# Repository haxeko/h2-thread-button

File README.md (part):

# ESP32-H2 Matter over Thread: nút nhấn chạy pin (CR2450 hoặc CR123A)

Thiết kế đầy đủ (phần cứng, firmware, tính pin, kiểm thử) cho một **nút nhấn Matter over Thread chạy một viên pin lithium 3 V**: module **ESP32-H2-WROOM-02C**, một nút nhấn vật lý, gửi **nhấn một lần / nhấn đúp / giữ lâu** dưới dạng sự kiện chuẩn của cluster **Switch** (device type Generic Switch 0x000F), dùng được trong Apple Home, Home Assistant và các controller Matter khác. Thiết bị là **Thread Sleepy End Device (SED)** kiêm **Matter Intermittently Connected Device (ICD)**: ngủ Light-sleep giữa các lần nhấn mà vẫn giữ kết nối Thread, thức dậy bằng ngắt của nút.

Ba bản phần cứng, cùng mạch và cùng mã firmware, khác nhau ở pin, đế pin, tụ bulk và bố trí; bản mini còn đổi hai chân GPIO ([`hardware/`](hardware/README.md)):

| Bo | Pin | Bo (cả anten) | Tuổi pin dự tính, SIT / LIT (20 lần nhấn/ngày) | Firmware |
|---|---|---|---|---|
| [`hardware/module-cr2450`](hardware/module-cr2450/README.md) | **CR2450** 620 mAh, đế Keystone 3008 | 37,4 × 36,5 mm | ~11 / ~15 tháng | mặc định |
| [`hardware/module-cr123a`](hardware/module-cr123a/README.md) | **CR123A** 1500 mAh, đế Bulgin BX0123 | 42,4 × 33,5 mm | ~30 / ~41 tháng | `sdkconfig.defaults.cr123a` |
| [`hardware/module-cr123a-mini`](hardware/module-cr123a-mini/README.md) | **CR123A** 1500 mAh trong vỏ, dọc cạnh dưới bo (tiếp điểm của vỏ nối dây vào pad BAT+/BAT− ở mép dưới; nút ở mép trên) | **34,5 × 20,8 mm**: dài đúng một viên CR123A | ~30 / ~41 tháng | `sdkconfig.defaults.cr123a_mini` |

Firmware ([`firmware/`](firmware)): ESP-IDF v6.0.2 + esp-matter release/v1.6.1. Các biến thể: mặc định (bo CR2450, ICD SIT), `lit`, `cr123a`, `cr123a_mini`, `unique_setup`, `factory`, `pmdiag`, `debug`. Host test chạy được không cần ESP-IDF: máy trạng thái nút (17 kịch bản), gửi lại cử chỉ, cách báo % pin. **Chưa đo trên bo thật**: mọi số đo đánh dấu [AS] phải được thay bằng số đo theo [checklist](docs/test-checklist.md).

Bản cũ dùng pin CR2032 (bo 29,8 × 23,9 mm, Keystone 3034) và bo chip ESP32-H2 không dùng module (`hardware-chip/`) đã bỏ khỏi repo: tuổi pin CR2032 chỉ 4–5,5 tháng (mục 1.6). Xem lịch sử git, commit `dad9ded` là bản cuối có cả hai. Firmware cảm biến cửa [`matter-door-sensor`](https://github.com/haxeko/esp32-iot-project/tree/claude/matter-button-cr2032/ESP32-H2/matter-thread/matter-door-sensor) (repo esp32-iot-project) viết cho bo CR2032 cũ; mạch giống hệt nên chạy được trên các bo này (công tắc lưỡi gà hàn song song SW1; bo mini cần đổi chân LED và đo pin như mục 2.3).

> **Kết luận nhanh**
>
> - Pin lithium 3 V (Li-MnO2: CR2450, CR123A) **không cấp trực tiếp** được cho ESP32-H2 (VDD tối thiểu 3,0 V; pin chỉ ~2,85–3,0 V khi có tải và giảm dần về 2,0 V). Bắt buộc có **buck-boost TPS63900** (Iq 75 nA). CR2450 có điện trở trong 8–30 Ω nên cần thêm **tụ bulk ≥ 220 µF hiệu dụng** trên đường pin; CR123A dưới 1 Ω, không cần.
> - Dòng ngủ: ESP32-H2 Light-sleep 25–27 µA ở 3,3 V → **~35 µA tại pin**: đạt mục tiêu < 50 µA. Riêng mức sàn này đã giới hạn tuổi pin ở tối đa **~19 tháng (CR2450)** và **~51 tháng (CR123A)** dù không nhấn lần nào.
> - Tuổi pin dự tính (TX 0 dBm, 1 controller, 5–100 lần nhấn/ngày): **CR2450: 10,4–11,3 tháng ở SIT** (mặc định, chạy với mọi controller kể cả Apple Home), **12,2–15,7 tháng ở LIT** (Home Assistant có Battery Saver; Apple Home hiện chưa hỗ trợ). **CR123A: 28–31 tháng ở SIT, 33–43 tháng ở LIT.** Mục tiêu 6–12 tháng đạt với cả hai (CR2450 ở SIT sát 12 tháng).
> - Chọn bo: **CR2450** khi cần gọn (pin dày 5 mm, bo 37,4 × 30,5 mm); **CR123A** khi cần ~2,5 năm và chịu lạnh tốt hơn (pin Ø17 × 34,5 mm, bo 42,4 × 27,5 mm).
> - Phản hồi: sự kiện đầu tiên (`InitialPress`) rời anten **~25–40 ms** sau khi nhấn; sự kiện "nhấn một lần" mà Apple Home / Home Assistant dùng (`MultiPressComplete`) đi ra **350 ms sau khi nhả** (cửa sổ phân biệt nhấn đúp, chỉnh được; tắt nhấn đúp thì có ngay).

## Mục lục

1. [Đánh giá khả thi](#1-đánh-giá-khả-thi)
2. [Kiến trúc phần cứng](#2-kiến-trúc-phần-cứng)
3. [Sơ đồ nguyên lý và bảng kết nối](#3-sơ-đồ-nguyên-lý-và-bảng-kết-nối)
4. [BOM](#4-bom)
5. [Cấu hình Thread SED + Matter ICD](#5-cấu-hình-thread-sed--matter-icd)
6. [Thuật toán nút nhấn](#6-thuật-toán-nút-nhấn)
7. [Firmware](#7-firmware)
8. [Build, flash, commissioning (Windows PowerShell)](#8-build-flash-commissioning-windows-powershell)
9. [Bảng tính thời lượng pin](#9-bảng-tính-thời-lượng-pin)
10. [Rủi ro và cách khắc phục](#10-rủi-ro-và-cách-khắc-phục)

Cấu trúc repo:

```
h2-thread-button/
├── README.md                 tài liệu chính (file này)
├── firmware/                 dự án ESP-IDF / esp-matter, chung cho mọi bo (mục 7)
├── hardware/                 các bo KiCad, mỗi bo một thư mục + bộ script sinh dùng chung (hardware/README.md)
│   ├── scripts/
│   ├── module-cr2450/
│   ├── module-cr123a/
│   └── module-cr123a-mini/
├── docs/                     test-checklist.md, sơ đồ nguyên lý (ảnh)
└── tools/                    mô hình pin, mô phỏng tụ bulk, vẽ sơ đồ, công cụ factory data (matter-mfg)
```

Kiểm thử: [`docs/test-checklist.md`](docs/test-checklist.md). PCB KiCad và file sản xuất: [`hardware/`](hardware/README.md).

Ký hiệu nguồn số liệu dùng trong toàn tài liệu: **[DS]** datasheet; **[ME]** số đo công bố của Espressif (esp-matter `examples/icd_app`, ESP32-H2 DevKitC); **[AS]** giả định / ước lượng, phải đo lại trên bo thật.

---

## 1. Đánh giá khả thi

### 1.1 Số liệu đầu vào

| Thông số | Giá trị | Nguồn |
|---|---|---|
| CR2450: điện áp danh định, dung lượng | 3,0 V; 620 mAh tới 2,0 V (Energizer, Panasonic, Murata; Renata CR2450N 540 mAh) | [DS] |
| CR2450: điện áp có tải | ~2,9 V phần lớn đời pin ở tải nhẹ; tụt nhanh sau ~85 % dung lượng | [DS] đồ thị xả |
| CR2450: điện trở trong | ~8–10 Ω khi mới, ~12–15 Ω giữa đời, 20–30 Ω gần cuối; ×2–2,5 ở −10 °C | [AS] đường IR của CR2032 (Energizer) chia theo diện tích điện cực (`tools/capsim.py`) |
| CR123A (IEC CR17345): điện áp, dung lượng | 3,0 V; 1400–1550 mAh tới 2,0 V (Panasonic CR123A, Energizer EL123AP, Duracell) | [DS] |
| CR123A: điện trở trong | ~0,1–0,3 Ω khi mới, dưới 1 Ω gần suốt đời pin; chịu xung 1–2 A | [DS] đồ thị xung / [AS] |
| Tự xả, nhiệt độ | ~1 %/năm; −30…60 °C (CR2450), −40…60 °C (CR123A) | [DS] |
| ESP32-H2: điện áp cấp (VDD3P3, VBAT, VDDPST) | **3,0–3,6 V** (typ 3,3 V) | [DS] ESP32-H2 v1.3, Bảng 5-2 |
| ESP32-H2: TX 802.15.4 | 36 mA @ 0 dBm; 60 mA @ 9 dBm; **140 mA @ 20 dBm** | [DS] Bảng 5-7 |
| ESP32-H2: RX 802.15.4 / BLE | 25 mA / 24 mA | [DS] Bảng 5-6, 5-7 |
| ESP32-H2: CPU 96 MHz, clock ngoại vi tắt | 10 mA chạy, 6 mA idle | [DS] Bảng 5-8 |
| ESP32-H2: Light-sleep (CPU, radio, ngoại vi số tắt nguồn) | **25 µA** typ (85 µA nếu giữ ngoại vi) | [DS] Bảng 5-9 |
| ESP32-H2: Light-sleep đo thực tế | 26,7–27,0 µA | [ME] |
| ESP32-H2: Deep-sleep | 7 µA (mất RAM, mất kết nối Thread) | [DS] |
| ESP32-H2: brownout | mức 7 ≈ 2,94 V (firmware chọn mức này) | ESP-IDF Kconfig |
| ESP32-H2: ADC, ATTEN 12 dB | 0–3300 mV, sai số ±23 mV sau hiệu chuẩn; dòng rò chân ≤ 50 nA | [DS] |
| TPS63900: dải vào, UVLO | 1,8–5,5 V; UVLO lên 1,75 V typ, trễ 0,1 V → tắt ở ~1,65 V | [DS] TI SLVSET3D |
| TPS63900: dòng tĩnh | 75 nA typ, 1 µA max | [DS] |
| TPS63900: hiệu suất, 3,3 V ra | ~89–91 % (VIN 2,5–3,3 V, tải 10 µA–10 mA); ~87 % ở VIN 1,8 V | [DS] Hình 8-7 |

### 1.2 Pin lithium 3 V có cấp trực tiếp cho ESP32-H2 được không? Không

1. **Điện áp.** ESP32-H2 cần ≥ 3,0 V. Pin Li-MnO2 (CR2450, CR123A) chỉ 3,0–3,3 V khi hở mạch lúc còn mới, ~2,85–3,0 V khi có tải và giảm dần về 2,0 V. Nối trực tiếp thì chip chạy **ngoài thông số ngay từ đầu**, và brownout (mức thấp nhất 2,57 V) cắt khi pin còn phần lớn dung lượng. Điều này đúng cả với CR123A dù pin chịu dòng tốt.
2. **Dòng (CR2450).** Xung TX/RX 25–36 mA (0 dBm) qua điện trở trong 8–30 Ω gây sụt 0,2–1 V; ở +20 dBm (140 mA, mặc định của driver ESP-IDF) sụt 1–4 V → reset ở mỗi khung phát. CR123A (< 1 Ω) chỉ sụt vài chục mV.
3. **Chân VBAT của module không phải đầu vào pin.** Trong WROOM-02C, chân 14 (VBAT) nối sẵn vào 3V3 qua điện trở 0 Ω (datasheet module, mục 8: *"When VBAT is powered by external battery, R2 can be NC"*). Đưa pin vào chân này là chập pin với đường 3V3.

→ Cần bộ **buck-boost** giữ 3,3 V khi pin đi từ 3,2 V xuống ~1,8 V. LDO không dùng được (pin < 3,3 V). Boost thuần không hạ áp được khi pin mới (3,2 V gần bằng đầu ra). Chọn **TI TPS63900**: Iq 75 nA (≈ 0,2 % của mức sàn 35 µA), hiệu suất ~90 % ở dòng µA–mA, đầu vào tới 1,8 V.

### 1.3 Dòng rút từ pin khi phát/thu

Bộ buck-boost là **tải công suất không đổi**: I_pin = I_3V3 × 3,3 V / (η × V_pin). Pin càng yếu, dòng rút càng lớn.

| Trạng thái (dòng ở 3,3 V [DS]) | V_pin 2,9 V | V_pin 2,4 V | V_pin 2,0 V |
|---|---|---|---|
| TX 0 dBm (36 mA) | 46 mA | 55 mA | 68 mA |
| RX (25 mA) | 32 mA | 38 mA | 47 mA |
| CPU 96 MHz (10 mA) | 13 mA | 15 mA | 19 mA |
| TX +9 dBm (60 mA) | 76 mA | 92 mA | 114 mA |
| TX +20 dBm (140 mA) | 177 mA | 214 mA | 266 mA |

(η = 0,90 ở 2,9 V và 2,4 V; 0,87 ở 2,0 V.) **Firmware giữ TX ở 0 dBm** (`THREAD_TX_POWER_DBM`) và áp dụng ngay khi driver 802.15.4 khởi tạo, trước khung đầu tiên (mục [5.6](#56-công-suất-phát)). BLE (chỉ dùng lúc ghép nối) cũng đặt 0 dBm.

### 1.4 Sụt áp, tụ bulk và brownout khi phát

Mô hình: pin = nguồn V_oc nối tiếp R_trong. TPS63900 tắt khi V_pin < ~1,65 V (UVLO), lúc đó 3V3 sập và ESP32-H2 brownout.

**CR2450** (bo `module-cr2450`):

- **Không có tụ bulk**, pin đã dùng ~80 % (V_oc ≈ 2,8 V, R ≈ 20 Ω [AS]): xung TX 0 dBm 55 mA → sụt 1,1 V → V_pin ≈ 1,7 V, sát UVLO; lạnh hoặc pin kém hơn thì **reset ở mỗi lần phát**.
- **Có tụ bulk C trên đường pin** (trước buck-boost): tụ cấp phần lớn xung ngắn, pin nạp lại tụ qua R. Sụt áp sau thời gian t: ΔV = I·R·(1 − e^(−t/RC)). Khung 802.15.4 dài nhất 127 byte = **4,3 ms** ở 250 kbit/s. Với C = 260 µF hiệu dụng, R = 20 Ω (τ = 5,2 ms): ΔV = 1,1 V × (1 − e^(−0,83)) = **0,62 V** → V_pin ≈ 2,2 V > UVLO. Thiết kế dùng **2 × 220 µF 1210 X5R** (≈ 260 µF hiệu dụng ở 3 V sau DC-bias [AS], kiểm tra bằng Murata SimSurfing hoặc đo).
- Đặt tụ **phía pin** (được phép sụt từ 2,9 V xuống ~1,8 V) dùng năng lượng tụ hiệu quả hơn nhiều so với phía 3,3 V (chỉ được sụt 0,3 V trước brownout 2,94 V).
- **Thu liên tục** khi re-attach Thread (Parent Request tới router rồi tới REED: 0,75 s + 1,25 s ≈ 2 s RX) thì không tụ nào bù được: pin phải tự cấp ~95 mW (25 mA × 3,3 V / η). Giữ V_pin ≥ 1,75 V đòi hỏi R_trong ≤ ~20 Ω (V_oc 2,8 V). Mô hình pin vì vậy chỉ tính **80 % dung lượng danh định** (496 mAh) [AS]. Qua mức đó nút vẫn chạy (xung ngắn vẫn có tụ đỡ), nhưng một lần re-attach (mất Border Router, khởi động lại) có thể gây brownout.

**CR123A** (bo `module-cr123a`): R_trong dưới 1 Ω gần suốt đời pin, nên mọi xung (TX, RX 2 s, khởi động) chỉ sụt 0,05–0,4 V. Mô phỏng `tools/capsim.py` [AS] cho V_pin thấp nhất ≥ 2,55 V khi khởi động hoặc re-attach ở mọi trạng thái pin tới −10 °C, **có hay không có tụ bulk**. Bo chỉ có 1 × 100 µF (lọc gần đầu vào, đường VBAT dài) cùng 10 µF ở VIN của TPS63900. Mô hình tính **90 %** dung lượng (1350 mAh).

**Firmware bảo vệ thêm (mọi bo):** brownout 2,94 V trên đường 3,3 V; bộ đếm brownout và đo áp lúc khởi động → Deep-sleep 1 giờ khi pin quá yếu (không reset lặp vô hạn); từ chối tải OTA khi pin không ở mức OK; đo điện trở trong mỗi ngày để báo pin yếu **trước** khi sập (mục [2.5](#25-đo-pin-gần-như-không-tốn-dòng)).

### 1.5 Dòng ngủ là giới hạn chính

Dòng trung bình, SIT 15 s, 20 lần nhấn/ngày, 1 controller (`tools/battery_model.py --breakdown`):

| Thành phần | Tại 3,3 V | Tỷ lệ |
|---|---|---|
| Light-sleep ESP32-H2 | 27,0 µA | 58,6 % |
| Data poll mỗi 15 s (0,25 mC/lần) | 16,7 µA | 36,2 % |
| Report keep-alive mỗi giờ | 0,9 µA | 1,9 % |
| Bảo trì Thread/Matter (SRP, MLE, đo pin, hỏi OTA) | 0,7 µA | 1,5 % |
| 20 lần nhấn/ngày | 0,9 µA | 1,9 % |
| **Tổng tại 3,3 V** | **46,1 µA** | |
| **Tại pin** (× 3,3 / (0,89 × V_pin) + Iq + rò) | **60 µA** (CR2450) / **59 µA** (CR123A) | → **11,2 tháng** / **30,4 tháng** |

Chỉ riêng Light-sleep (không poll, không nhấn) đã là ~35 µA tại pin → trần **~18,8 tháng** với CR2450 (496 mAh dùng được), **~51 tháng** với CR123A (1350 mAh). Với CR2450, muốn ≥ 12 tháng ở SIT thì dòng trung bình tại pin phải ≤ ~56 µA: dùng LIT (chỉ Home Assistant), hoặc bo CR123A.

**Vì sao không dùng Deep-sleep (7 µA)?** Deep-sleep tắt RAM, mất trạng thái Thread và phiên Matter. Mỗi lần nhấn sẽ phải khởi động lại, attach Thread (≥ 2 s thu), mở lại phiên CASE và subscription (vài giây): **không đạt < 300 ms**, controller thấy thiết bị offline giữa các lần nhấn, và mỗi lần nhấn tốn 60–200 mC (bằng 2–8 giờ Light-sleep).

### 1.6 Kết luận và phương án

| Mục tiêu | Thiết kế này | Đạt? |
|---|---|---|
| Dòng ngủ < 50 µA | 27 µA tại 3,3 V; ~35 µA tại pin | ✅ |
| Phản hồi < 300 ms | `InitialPress` rời anten ~25–40 ms sau khi nhấn; "nhấn một lần" = lúc nhả + 350 ms (chỉnh được, mục [6.6](#66-độ-trễ)) | ✅ có điều kiện |
| Pin 6–12 tháng | CR2450: SIT 10,4–11,3 tháng, LIT 12,2–15,7 tháng; CR123A: SIT 28–31 tháng, LIT 33–43 tháng | ✅ (CR2450 ở SIT sát 12 tháng) |

Các nguồn pin đã xét (20 lần nhấn/ngày, 1 controller, cùng mạch và firmware, `tools/battery_model.py`):

| Nguồn | SIT 15 s (Apple + HA) | LIT 120 s (HA Battery Saver) | Ghi chú |
|---|---|---|---|
| **CR2450** (bo `module-cr2450`) | **11,2 tháng** | **15,0 tháng** | 620 mAh × 0,80; Ø24,5 × 5,0 mm; bo gọn nhất |
| **CR123A** (bo `module-cr123a`, `module-cr123a-mini`) | **30,4 tháng** | **40,7 tháng** | 1500 mAh × 0,90; Ø17 × 34,5 mm; chịu xung và lạnh tốt |
| CR2032 (bo cũ, đã bỏ) | 4,0 tháng | 5,4 tháng | 220 mAh × 0,80: lý do bỏ |
| 2 × AAA alkaline (chưa có bo) | ~19 tháng | ~26 tháng | TPS63900 chạy tới 1,8 V (0,9 V/cell); pin alkaline có thể chảy |
| CR2450 + SoC dòng ngủ ~2 µA | 23,9 tháng | 53,4 tháng | chỉ đổi mức sàn, vẫn giữ chi phí poll của ESP32-H2 (phải thiết kế lại phần cứng và firmware) |

---

## 2. Kiến trúc phần cứng

### 2.1 Sơ đồ khối

```
            Q1 P-FET                 VBAT (1,8 .. 3,2 V)                   3V3
 Pin ─────► chống ngược ──JP1──┬────────────────┬──► TPS63900 ──JP2──┬──► ESP32-H2-WROOM-02C
 (BT1)      cực              C1(+C2)          R9 1 MΩ   buck-boost       │      GPIO10 ◄── SW1 (LP IO, EXT1 wake)
 CR2450 /                    tụ bulk           │        3,3 V, Iq 75 nA  │      GPIO22 ──► LED D1
 CR123A                      (theo bo)         └──────── VBAT_SENSE ─────┼────► GPIO1 (ADC1_CH0)
                                                                         │      UART0, EN, BOOT, USB ──► pad nạp/debug
                                                                       C4..C6
```

| Khối | Nhiệm vụ |
|---|---|
| Q1 (P-MOSFET) | chống lắp ngược pin, sụt ~5 mV (R_DS(on) ~0,1 Ω ở 50 mA) thay vì 0,3 V của diode Schottky |
| JP1, JP2 (cầu hàn) | điểm cắt để đo dòng pin (JP1) và dòng đường 3,3 V (JP2); mặc định nối |
| C1, C2 | tụ bulk, cấp xung TX/RX ngắn, giảm sụt áp trên điện trở trong của pin (mục 1.4): bo CR2450 2 × 220 µF; bo CR123A chỉ C1 100 µF; bo CR123A mini chỉ C1 22 µF |
| TPS63900 | buck-boost 3,3 V, Iq 75 nA, chạy từ 1,8 V |
| R9 + C9 | đo áp pin không tốn dòng (mục 2.5) |
| SW1 + R6/R7/C8 | nút nhấn, lọc RC, kéo lên 1 MΩ (mục 2.4) |
| D1 + R8 | LED trạng thái (ghép nối, Identify, xác nhận reset, pin yếu); chỉ nháy ngắn |

### 2.2 Đường nguồn

- **Q1 AO3401A** nối kiểu "ideal diode": D về pin, S về VBAT, G xuống GND. Lắp đúng: diode thân dẫn trước, V_GS = −V_pin → FET mở. Lắp ngược: V_GS = 0, diode thân phân cực ngược → không có dòng. Cần thiết vì cả hai đế đều lắp ngược pin được: với đế Keystone 3008 (CR2450), lá kẹp (+) chạm mặt trên của pin, lắp úp pin thì mặt (−) chạm lá kẹp (+), mặt (+) chạm pad GND; đế Bulgin BX0123 (CR123A) cho cắm ngược đầu pin.
- **TPS63900** (theo mạch điển hình 3,3 V của datasheet, Hình 8-1 / Bảng 8-5):
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
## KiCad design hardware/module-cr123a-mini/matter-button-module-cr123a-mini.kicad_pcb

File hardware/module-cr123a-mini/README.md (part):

# Bo module-cr123a-mini: nút nhấn Matter dài đúng một viên CR123A

Bản gọn của [`module-cr123a`](../module-cr123a/README.md): bo **dài 34,5 mm, bằng chiều dài pin CR123A**, cao 14,8 mm. Anten module chìa ra 6 mm ở mép trên, **cả cụm 34,5 × 20,8 mm**. **Nút nhấn SW1 và LED ở mép trên (phía anten)**, góc trái, xa anten nhất. Pin **không nằm trên bo**: pin nằm trong ngăn pin của vỏ, **dọc cạnh dưới bo** (cạnh không có anten); hai tiếp điểm của vỏ nối dây vào hai pad **BAT+ / BAT−** ở hai đầu mép dưới, mặt dưới bo.

Mọi file được sinh bằng các script dùng chung trong [`../scripts`](../README.md) từ [`design.py`](design.py), rồi kiểm tra bằng KiCad 9.0.9:

- **ERC: 0 lỗi, 0 cảnh báo.**
- **DRC: 0 vi phạm, 0 pad chưa nối, 0 lỗi footprint, 0 lệch giữa PCB và schematic.**
- **Mọi đường mạch đều vẽ tay** trong `design.py`, không qua FreeRouting: sinh lại lúc nào cũng ra đúng bo này.

Chưa đặt mạch, chưa đo trên bo thật. Firmware: **`sdkconfig.defaults.cr123a_mini`**, không dùng bản `cr123a` vì LED và chân đo pin khác (mục 2).

| Mặt trên | Mặt dưới |
|---|---|
|  |  |

Đồng và silkscreen (mặt dưới nhìn từ dưới lên, đã lật):

## 1. Khác bo module-cr123a

| | `module-cr123a` | `module-cr123a-mini` |
|---|---|---|
| Bo / cả cụm có anten | 42,4 × 27,5 / 42,4 × 33,5 mm | **34,5 × 14,8 / 34,5 × 20,8 mm** |
| Pin | trong đế Bulgin BX0123 ở mặt dưới bo | trong vỏ, dọc cạnh dưới bo; tiếp điểm của vỏ nối dây vào pad BAT+ / BAT− ở mép dưới |
| Nút SW1, LED | SW1 ở dải dưới, giữa; LED dưới module, cạnh chân 15 | **mép trên (phía anten), góc trái**; LED ngay bên phải nút |
| Lắp ráp | linh kiện mặt trên, đế pin mặt dưới | **chỉ mặt trên**; mặt dưới chỉ có đồng: 2 pad pin, 8 pad test |
| LED / đo pin | GPIO22 (chân 15) / GPIO1 (chân 27, ADC1_CH0) | **GPIO11 (chân 6) / GPIO4 (chân 3, ADC1_CH3)** |
| Đo dòng | cầu hàn JP1 (pin), JP2 (3,3 V) | **mắc ampe kế nối tiếp dây BAT+**; không có JP1, JP2 |
| Tụ VBAT | C1 100 µF 1206 | C1 22 µF 0603 (cùng mã với C4) |
| C7 (tụ EN, không lắp) | có footprint | bỏ (module đã có RC trên EN) |
| Pad test | 10 (thêm VBAT, VBAT_SENSE) | 8: 3V3, GND, TX, RX, EN, BOOT, USB D−, D+ (VBAT đo ở C1, VBAT_SENSE ở C9) |
| Firmware | `sdkconfig.defaults.cr123a` | `sdkconfig.defaults.cr123a_mini` |
| Tuổi pin dự tính | ~30 tháng (SIT), ~41 tháng (LIT) | như bản kia: cùng pin, cùng mạch |

## 2. Vì sao đổi chân LED và đo pin

Mọi linh kiện phải nằm ở mặt trên, trong vùng 15 × 14,2 mm bên trái module. Chân 15 (GPIO22) nằm ở cạnh dưới module, sát mép dưới bo, không còn chỗ thoát dây. Chân 27 (GPIO1) nằm ở cạnh phải module, xa phần mạch. Bo này chỉ dùng các chân ở cạnh trái module:

| Chân module | GPIO | Dùng cho |
|---|---|---|
| 1 | 3V3 | nguồn, C6 |
| 2 | EN | R4, pad test EN |
| 3 | **GPIO4 (ADC1_CH3)** | **đo pin**: R9 1 MΩ từ VBAT, C9 100 nF |
| 5 | GPIO10 | nút (LP IO, đánh thức EXT1), như các bo khác |
| 6 | **GPIO11** | **LED**: R8 1 kΩ → D1 |
| 7 | GPIO8 | R5 kéo lên (strapping) |
| 8 | GPIO9 | BOOT, pad test |

GPIO4 là chân JTAG MTCK. Lúc chạy, driver ADC đặt chân ở chế độ analog (không có điện trở kéo), và trong Light-sleep firmware cô lập mọi GPIO. Chỉ lúc khởi động hay Deep-sleep, nếu chân có điện trở kéo mặc định thì tốn tối đa vài µA qua R9: cần đo (checklist, mục P). GPIO11 là LP IO thường, không phải chân strapping hay JTAG.

## 3. Thông số bo

| Mục | Giá trị |
|---|---|
| Kích thước | **34,5 × 14,8 mm**, góc bo R0,5; anten module nhô 6 mm khỏi mép trên → **34,5 × 20,8 mm**; không có lỗ |
| Lớp | 2 lớp FR-4 1,6 mm, đồng 1 oz |
| Đường mạch | 0,2 mm tín hiệu, 0,25–0,5 mm nguồn; khe hở ≥ 0,2 mm; via 0,6 / 0,3 mm phủ mask |
| Cách mép bo | đồng ≥ 0,3 mm |
| Bề mặt | ENIG khuyến nghị (WSON bước 0,5 mm, pad hàn dây) |
| Linh kiện | **mặt trên tất cả** (lắp ráp một mặt) |
| Mặt dưới | pad BAT+ 3,6 × 1,6 mm và pad BAT− 2,8 × 1,6 mm dọc mép dưới, ở hai đầu (BAT− nằm trong vùng phủ GND), 8 pad test Ø1,5 mm dưới module, phủ đồng GND |

## 4. Bố trí

| Vùng (nhìn từ mặt trên) | Linh kiện |
|---|---|
| Mép trên, góc trái (phía anten) | SW1, LED D1 ngay bên phải nút; thân nút cách mép trái module (và anten) hơn 10 mm. Đường nút chạy dọc mép trên, qua phía trên D1, xuống ở x = 10,2 mm tới R7; đường LED xuống ở x = 9,6 mm tới R8 |
| Giữa, bên trái | TPS63900: L1 sát mép trái, C4 (3V3) phía trên, C3 (VIN) phía dưới, R1–R3 bên phải; cùng mạch như các bo khác, xoay 90° theo chiều kim đồng hồ, C3 và C4 sát U2 hơn. C5 (3V3) giữa nút và L1 |
| Mép dưới, bên trái | Q1 + C1: đầu vào pin, cực D của Q1 ngay trên pad BAT+ (mặt dưới); đường VBAT dọc y = 10,6 mm nối Q1, C3, C1, chân SEL/EN của U2 |
| Cạnh trái module | mỗi chân một hàng: C6 (chân 1), R4 (chân 2), R9 + C9 (chân 3), R7 + C8 (chân 5), R8 (chân 6), R5 (chân 7); R6 (kéo lên nút) ở trên cùng, giữa đường nút và trục 3V3 theo mép trên tới chân 1 |
| Mặt dưới | BAT+ và BAT− dọc mép dưới, ở hai đầu; pad test dưới module; 3V3 từ bộ nguồn sang góc module (rồi tới TP1 và xuống R5) và VBAT tới R9 đi ở mặt dưới |

Tọa độ (mm, gốc ở góc trên trái, nhìn từ mặt trên; nhìn từ mặt dưới thì trái/phải đảo lại):

| Vật | Tọa độ |
|---|---|
| Tâm nút SW1 (thân 4,2 × 3,2 mm) | (2,95; 1,95): thân cách mép trên 0,35 mm, cách mép trái 0,85 mm |
| Tâm LED D1 | (7,35; 1,55) |
| Pad BAT+ (mặt dưới) | tâm (2,4; 13,4), 3,6 × 1,6 mm |
| Pad BAT− (mặt dưới) | tâm (32,5; 13,4), 2,8 × 1,6 mm (cách BAT+ 30,1 mm) |
| Pad test, hàng trên (y = 9,6) | x = 19,5 EN · 22,0 3V3 · 27,0 USB D+ · 29,5 USB D− |
| Pad test, hàng dưới (y = 12,2) | x = 19,5 BOOT · 22,0 GND · 27,0 TXD0 · 29,5 RXD0 |
| Module | thân x = 15,7 … 33,7, y = −6 … 14; mép anten y = −6, chân anten y = 0 (mép bo) |

## 5. Lắp vào vỏ

- **Pin nằm dọc cạnh dưới bo** (cạnh không có anten), trục pin song song cạnh dài: sau nửa dưới của bo hoặc ngay dưới mép dưới, tùy vỏ. Ngăn pin và hai tiếp điểm (lò xo cho cực −, tấm phẳng cho cực +) thuộc vỏ. Hàn dây từ tiếp điểm + vào **pad BAT+ (mép dưới, đầu trái)**, từ tiếp điểm − vào **pad BAT− (mép dưới, đầu phải)**: hai pad ở ngay hai đầu pin, dây ngắn.
- **Nút**: SW1 nhấn từ mặt trên, ở góc trên trái (mép phía anten); nút bấm của vỏ đặt ngay trên SW1 (thân 4,2 × 3,2 mm, cao 2,5 mm), LED D1 ngay bên phải.
- **Lót cách điện** (Kapton, tấm nhựa 0,1–0,2 mm) nếu pin áp vào mặt dưới bo: vỏ thép của CR123A là cực −, mặt dưới bo có pad test và pad pin để hở đồng.
- **Lắp ngược pin** vẫn an toàn nhờ Q1. Nên làm vỏ chỉ cho pin lắp một chiều (cực + lõm vào), đỡ phải tháo ra lắp lại.
- **Anten**: pin (vỏ kim loại) và dây pin ở phía mép dưới, xa mép trên; không để pin hay dây trồi lên phía anten. Không đặt kim loại trong ~15 mm quanh anten. Đo RSSI/LQI của parent khi đã đóng vỏ (checklist mục C).
- **Đo dòng**: tháo dây BAT+ khỏi pad và mắc ampe kế (PPK2, Joulescope) vào giữa (checklist mục F). Không có JP1/JP2 như các bo khác.
- **Nạp firmware**: dùng pogo-pin vào các pad test ở mặt dưới **trước khi lắp vào vỏ**, cấp nguồn bằng pin hoặc nguồn 3,0 V vào BAT+/BAT−.

## 6. Đặt mạch và lắp ráp

1. **PCB**: tải `fab/matter-button-module-cr123a-mini-gerber.zip` lên JLCPCB/PCBWay: 2 lớp, 1,6 mm, ENIG.
2. **Lắp ráp JLCPCB (tùy chọn, một mặt)**: chọn lắp mặt trên với `fab/bom-jlcpcb.csv` và `fab/cpl-jlcpcb.csv`: 10 loại Basic, 4 loại Extended (U2 C1518762, L1 C391305, R1 C49010116, SW1 C116501). Kiểm tra góc xoay ở bản xem trước (U2, Q1, D1, L1, SW1).
3. **U1 hàn tay** (LCSC không có), như các bo khác.
4. Hàn dây pin (mục 5), nạp firmware bản `cr123a_mini` ([README chính mục 8](../../README.md#8-build-flash-commissioning-windows-powershell)), chạy [checklist](../../docs/test-checklist.md) (mục P cho bo này).

## 7. File

| File | Nội dung |
|---|---|
| `design.py` | nguồn duy nhất của bo: mạch (thay đổi so với `../scripts/circuit.py`), viền bo, vị trí, toàn bộ đường mạch, via, chữ in |
| `matter-button-module-cr123a-mini.kicad_pro/.kicad_sch/.kicad_pcb` | dự án KiCad 9 |
| `lib/` | symbol + footprint ESP32-H2-WROOM-02C, power symbol VBAT, footprint `CR123A_WirePads` (hai pad nối dây, sinh bởi `gen_project.py`) |
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
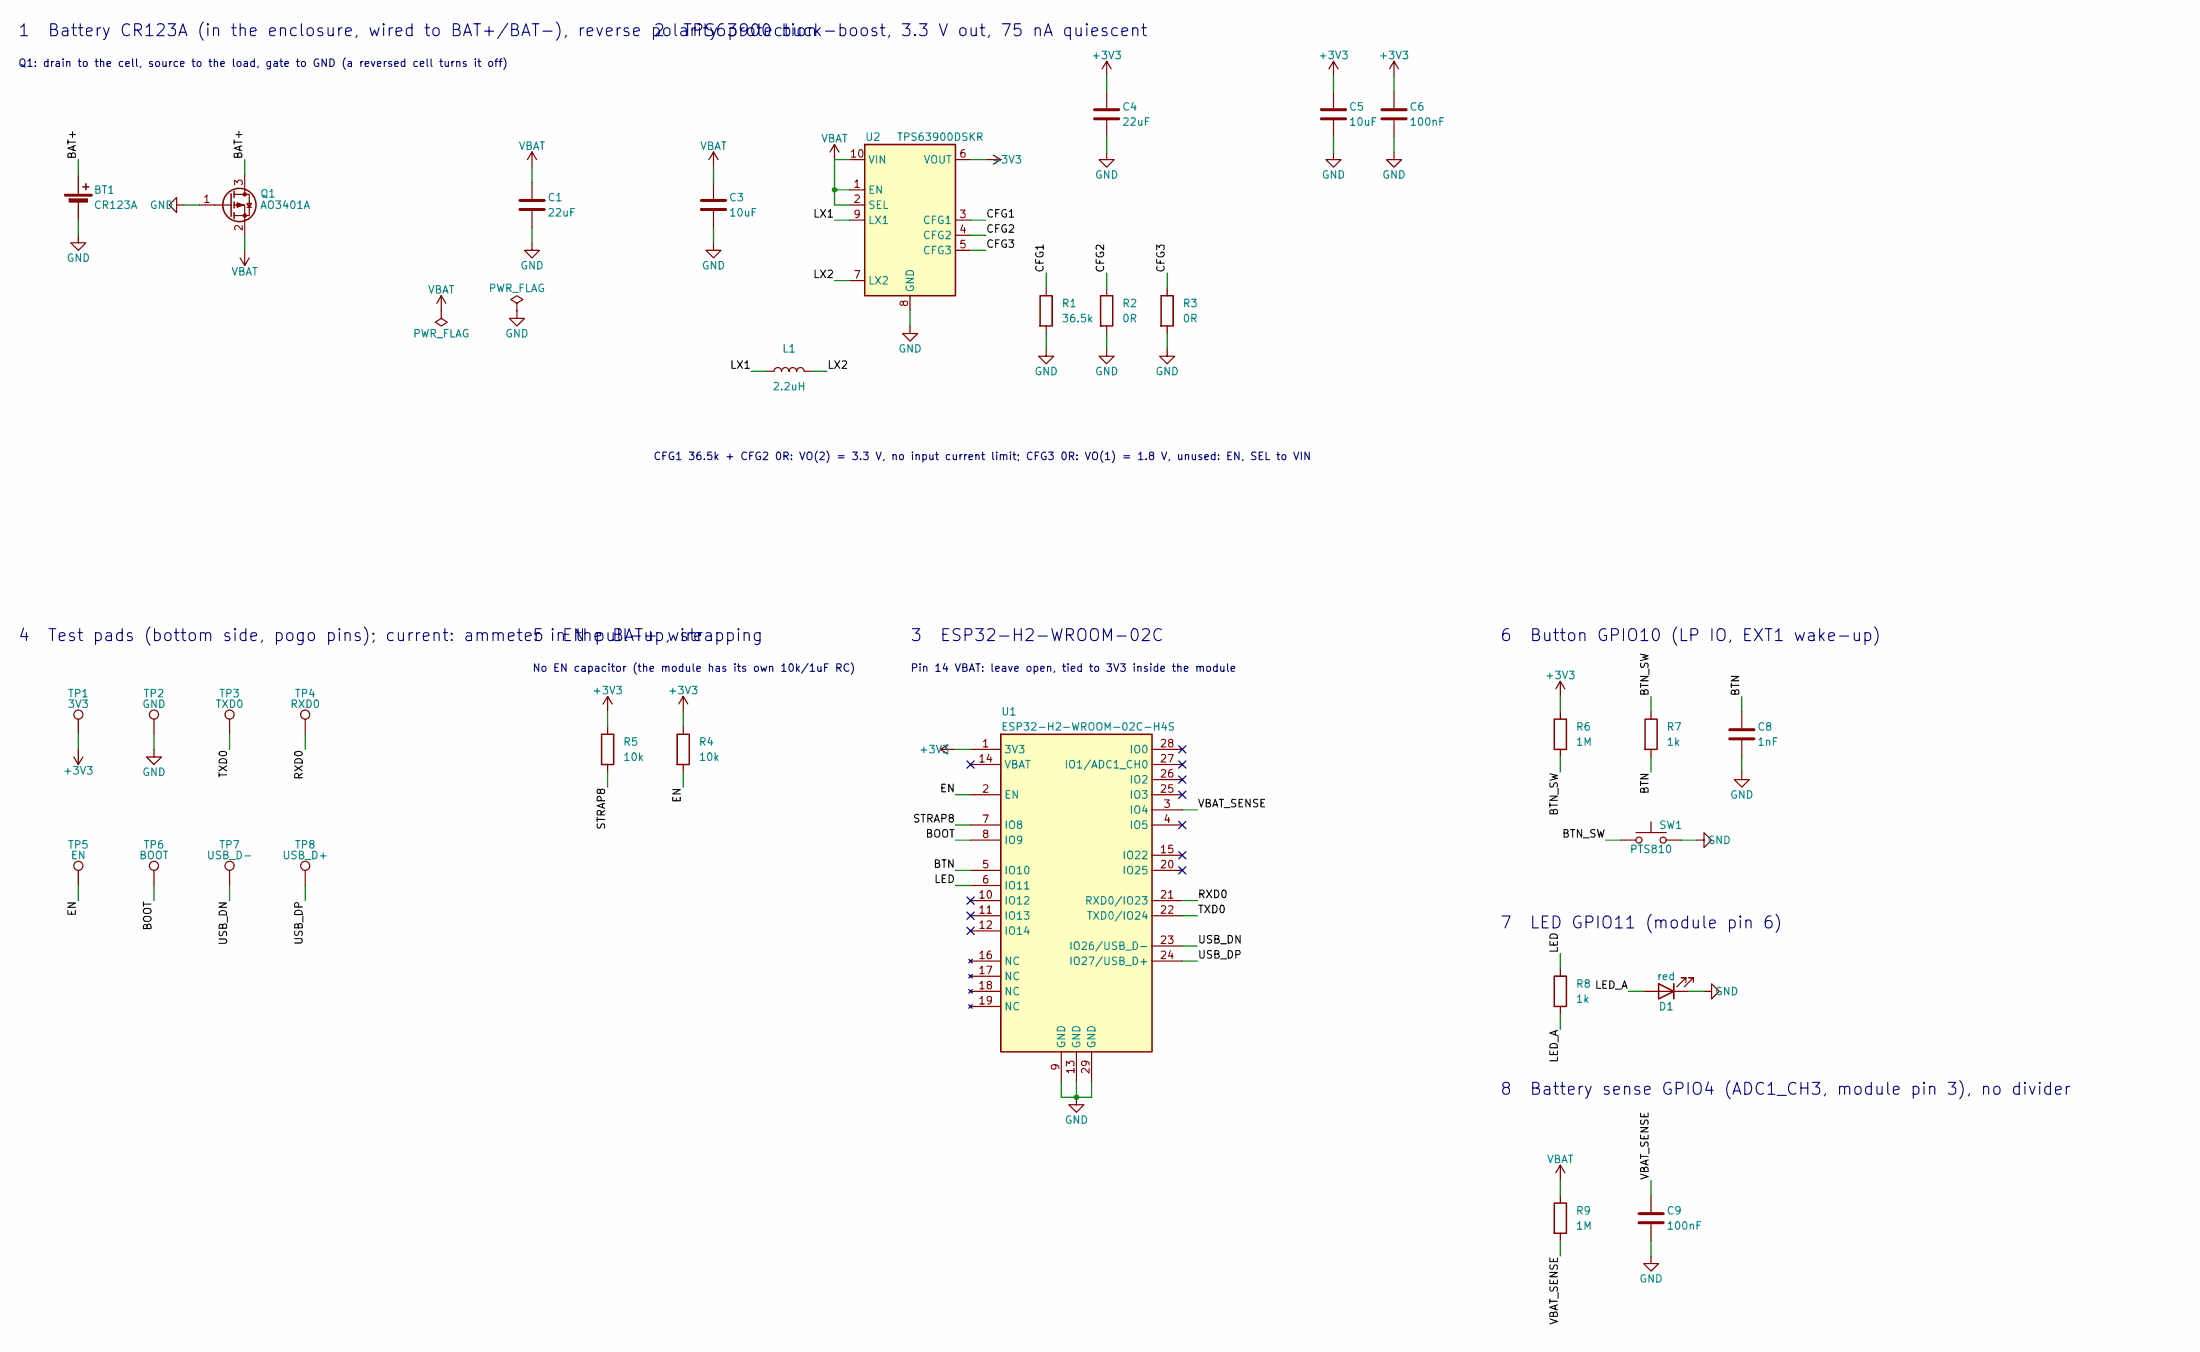
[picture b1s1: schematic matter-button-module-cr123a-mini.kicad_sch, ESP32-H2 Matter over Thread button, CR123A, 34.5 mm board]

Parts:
BT1: CR123A; CR123A_WirePads
C1, C4: 22uF; C_0603_1608Metric; MPN CL10A226MQ8NRNC; LCSC C59461
C3, C5: 10uF; C_0603_1608Metric; MPN CL10A106KP8NNNC; LCSC C19702
C6, C9: 100nF; C_0402_1005Metric; MPN CL05B104KO5NNNC; LCSC C1525
C8: 1nF; C_0402_1005Metric; MPN CL05B102KB5NNNC; LCSC C1523
D1: red; LED_0603_1608Metric; MPN KT-0603R; LCSC C2286
L1: 2.2uH; L_1008_2520Metric; MPN DFE252012P-2R2M=P2; LCSC C391305
Q1: AO3401A; SOT-23; MPN AO3401A; LCSC C15127
R1: 36.5k; R_0402_1005Metric; MPN FRC0402F3652TS; LCSC C49010116
R2, R3: 0R; R_0402_1005Metric; MPN 0402WGF0000TCE; LCSC C17168
R4, R5: 10k; R_0402_1005Metric; MPN 0402WGF1002TCE; LCSC C25744
R6, R9: 1M; R_0402_1005Metric; MPN 0402WGF1004TCE; LCSC C26083
R7, R8: 1k; R_0402_1005Metric; MPN 0402WGF1001TCE; LCSC C11702
SW1: PTS810; SW_SPST_PTS810; MPN PTS810 SJM 250 SMTR LFS; LCSC C116501
TP1: 3V3; TestPoint_Pad_D1.5mm
TP2: GND; TestPoint_Pad_D1.5mm
TP3: TXD0; TestPoint_Pad_D1.5mm
TP4: RXD0; TestPoint_Pad_D1.5mm
TP5: EN; TestPoint_Pad_D1.5mm
TP6: BOOT; TestPoint_Pad_D1.5mm
TP7: USB_D-; TestPoint_Pad_D1.5mm
TP8: USB_D+; TestPoint_Pad_D1.5mm
U1: ESP32-H2-WROOM-02C-H4S; ESP32-H2-WROOM-02C; MPN ESP32-H2-WROOM-02C-H4S
U2: TPS63900DSKR; WSON-10-1EP_2.5x2.5mm_P0.5mm_EP1.2x2mm; MPN TPS63900DSKR; LCSC C1518762

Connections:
+3V3: C4.1, C5.1, C6.1, R4.1, R5.1, R6.1, TP1.1, U1.1 (3V3), U2.6 (VOUT)
/BAT+: BT1.1 (+), Q1.3 (D)
/BOOT: TP6.1, U1.8 (IO9)
/BTN: C8.1, R7.2, U1.5 (IO10)
/BTN_SW: R6.2, R7.1, SW1.1
/CFG1: R1.1, U2.3 (CFG1)
/CFG2: R2.1, U2.4 (CFG2)
/CFG3: R3.1, U2.5 (CFG3)
/EN: R4.2, TP5.1, U1.2 (EN)
/LED: R8.1, U1.6 (IO11)
/LED_A: D1.2 (A), R8.2
/LX1: L1.1, U2.9 (LX1)
/LX2: L1.2, U2.7 (LX2)
/RXD0: TP4.1, U1.21 (RXD0/IO23)
/STRAP8: R5.2, U1.7 (IO8)
/TXD0: TP3.1, U1.22 (TXD0/IO24)
/USB_DN: TP7.1, U1.23 (IO26/USB_D-)
/USB_DP: TP8.1, U1.24 (IO27/USB_D+)
/VBAT_SENSE: C9.1, R9.2, U1.3 (IO4)
GND: BT1.2 (-), C1.2, C3.2, C4.2, C5.2, C6.2, C8.2, C9.2, D1.1 (K), Q1.1 (G), R1.2, R2.2, R3.2, SW1.2, TP2.1, U1.9 (GND), U1.13 (GND), U1.29 (GND), U2.8 (GND), U2.11 (GND)
VBAT: C1.1, C3.1, Q1.2 (S), R9.1, U2.1 (EN), U2.2 (SEL), U2.10 (VIN)

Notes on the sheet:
1 Battery CR123A (in the enclosure, wired to BAT+/BAT-), reverse polarity protection
Q1: drain to the cell, source to the load, gate to GND (a reversed cell turns it off)
2 TPS63900 buck-boost, 3.3 V out, 75 nA quiescent
CFG1 36.5k + CFG2 0R: VO(2) = 3.3 V, no input current limit; CFG3 0R: VO(1) = 1.8 V, unused: EN, SEL to VIN
4 Test pads (bottom side, pogo pins); current: ammeter in the BAT+ wire
5 EN pull-up, strapping
No EN capacitor (the module has its own 10k/1uF RC)
3 ESP32-H2-WROOM-02C
Pin 14 VBAT: leave open, tied to 3V3 inside the module
6 Button GPIO10 (LP IO, EXT1 wake-up)
7 LED GPIO11 (module pin 6)
8 Battery sense GPIO4 (ADC1_CH3, module pin 3), no divider

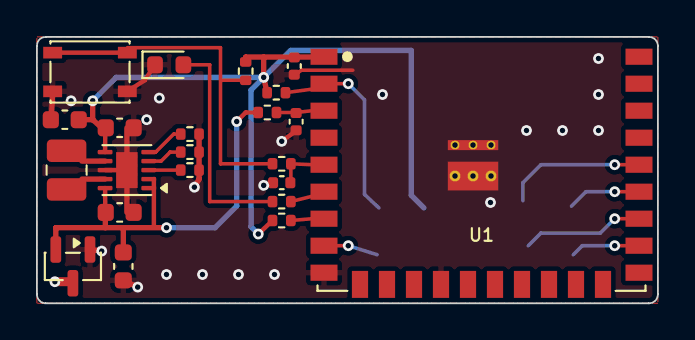
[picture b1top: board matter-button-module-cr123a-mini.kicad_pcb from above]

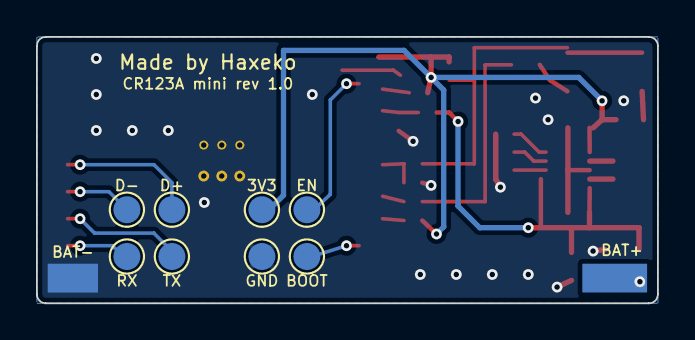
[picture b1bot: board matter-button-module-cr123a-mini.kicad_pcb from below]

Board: 2 copper layers, 34.5 x 14.8 mm, 31 parts (9 on the bottom side), 21 nets.

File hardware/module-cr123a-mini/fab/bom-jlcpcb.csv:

Comment,Designator,Footprint,LCSC Part #,Manufacturer Part Number
1nF,C8,0402,C1523,CL05B102KB5NNNC
22uF,"C1,C4",0603,C59461,CL10A226MQ8NRNC
10uF,"C3,C5",0603,C19702,CL10A106KP8NNNC
100nF,"C6,C9",0402,C1525,CL05B104KO5NNNC
red,D1,0603,C2286,KT-0603R
2.2uH,L1,1008,C391305,DFE252012P-2R2M=P2
AO3401A,Q1,SOT-23,C15127,AO3401A
36.5k,R1,0402,C49010116,FRC0402F3652TS
0R,"R2,R3",0402,C17168,0402WGF0000TCE
10k,"R4,R5",0402,C25744,0402WGF1002TCE
1M,"R6,R9",0402,C26083,0402WGF1004TCE
1k,"R7,R8",0402,C11702,0402WGF1001TCE
PTS810,SW1,SMD 4.2x3.2mm tact switch,C116501,PTS810 SJM 250 SMTR LFS
TPS63900DSKR,U2,WSON-10 2.5x2.5mm,C1518762,TPS63900DSKR

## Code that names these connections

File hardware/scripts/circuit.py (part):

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         lcsc="C391305", desc="Murata 2.5x2.0 mm, Isat 3 A", pins={"1": "LX1", "2": "LX2"}, sch=(160.02, 91.44, 90)),
    dict(ref="R1", lib="Device:R", value="36.5k", fp=R0402, mpn="FRC0402F3652TS", lcsc="C49010116",
         desc="1 %, CFG1: VO(2) 3.3 V",
         pins={"1": "CFG1", "2": GND}, sch=(203.2, 81.28, 0)),
    dict(ref="R2", lib="Device:R", value="0R", fp=R0402, mpn="0402WGF0000TCE", lcsc="C17168",
         desc="CFG2: no input current limit",
         pins={"1": "CFG2", "2": GND}, sch=(213.36, 81.28, 0)),
    dict(ref="R3", lib="Device:R", value="0R", fp=R0402, mpn="0402WGF0000TCE", lcsc="C17168",
         desc="CFG3: VO(1) 1.8 V, unused (SEL = VIN selects VO(2))",
         pins={"1": "CFG3", "2": GND}, sch=(223.52, 81.28, 0)),
    dict(ref="C4", lib="Device:C", value="22uF", fp=C0603, mpn="CL10A226MQ8NRNC", lcsc="C59461",
         desc="6.3 V X5R, at U2 VOUT",
         pins={"1": "VOUT", "2": GND}, sch=(213.36, 48.26, 0)),
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    # ---- module
    dict(ref="U1", lib=f"{LIB}:ESP32-H2-WROOM-02C", value="ESP32-H2-WROOM-02C-H4S",
         fp=f"{LIB}:ESP32-H2-WROOM-02C", mpn="ESP32-H2-WROOM-02C-H4S", lcsc="", desc="Thread/BLE module, 4 MB flash",
         pins={"1": V33, "14": "NC", "2": "EN", "7": "STRAP8", "8": "BOOT", "5": "BTN", "6": "NC", "10": "NC",
               "11": "NC", "12": "NC", "16": None, "17": None, "18": None, "19": None,
               "28": "NC", "27": "VBAT_SENSE", "26": "NC", "25": "NC", "3": "NC", "4": "NC", "15": "LED",
               "20": "NC", "21": "RXD0", "22": "TXD0", "23": "USB_DN", "24": "USB_DP",
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         pins={"1": "EN", "2": GND}, sch=(154.94, 154.94, 0), dnp=True),
    dict(ref="R5", lib="Device:R", value="10k", fp=R0402, mpn="0402WGF1002TCE", lcsc="C25744",
         desc="GPIO8 strapping pull-up",
         pins={"1": V33, "2": "STRAP8"}, sch=(129.54, 154.94, 0)),
    # ---- button (GPIO10, LP IO)
    dict(ref="R6", lib="Device:R", value="1M", fp=R0402, mpn="0402WGF1004TCE", lcsc="C26083", desc="button pull-up",
         pins={"1": V33, "2": "BTN_SW"}, sch=(289.56, 152.4, 0)),
    dict(ref="R7", lib="Device:R", value="1k", fp=R0402, mpn="0402WGF1001TCE", lcsc="C11702", desc="button series",
         pins={"1": "BTN_SW", "2": "BTN"}, sch=(304.8, 152.4, 0)),
    dict(ref="C8", lib="Device:C", value="1nF", fp=C0402, mpn="CL05B102KB5NNNC", lcsc="C1523",
         desc="50 V X7R, button filter",
         pins={"1": "BTN", "2": GND}, sch=(320.04, 152.4, 0)),
    dict(ref="SW1", lib="Switch:SW_Push", value="PTS810", fp="Button_Switch_SMD:SW_SPST_PTS810",
         mpn="PTS810 SJM 250 SMTR LFS", lcsc="C116501",
         desc="C&K 4.2x3.2 mm tact switch, 160 gf", pins={"1": "BTN_SW", "2": GND},
         sch=(304.8, 170.18, 0)),
    # ---- LED (GPIO22)
    dict(ref="R8", lib="Device:R", value="1k", fp=R0402, mpn="0402WGF1001TCE", lcsc="C11702", desc="LED series",
         pins={"1": "LED", "2": "LED_A"}, sch=(289.56, 195.58, 0)),
    dict(ref="D1", lib="Device:LED", value="red", fp="LED_SMD:LED_0603_1608Metric", mpn="KT-0603R",
         lcsc="C2286", desc="Hubei KENTO 0603 red", pins={"1": GND, "2": "LED_A"}, sch=(307.34, 195.58, 180)),
    # ---- battery sense (GPIO1)
    dict(ref="R9", lib="Device:R", value="1M", fp=R0402, mpn="0402WGF1004TCE", lcsc="C26083",
         desc="VBAT sense, no divider",
         pins={"1": VBAT, "2": "VBAT_SENSE"}, sch=(289.56, 233.68, 0)),
    dict(ref="C9", lib="Device:C", value="100nF", fp=C0402, mpn="CL05B104KO5NNNC", lcsc="C1525",
         desc="16 V X7R, VBAT sense filter",
         pins={"1": "VBAT_SENSE", "2": GND}, sch=(304.8, 233.68, 0)),
    # ---- test pads (bottom side)
    dict(ref="TP1", lib="Connector:TestPoint", value="3V3", fp=TP, mpn="", desc="test pad", pins={"1": V33},
         sch=(40.64, 152.4, 0)),
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    dict(ref="TP6", lib="Connector:TestPoint", value="BOOT", fp=TP, mpn="", desc="test pad", pins={"1": "BOOT"},
         sch=(53.34, 177.8, 0)),
    dict(ref="TP7", lib="Connector:TestPoint", value="USB_D-", fp=TP, mpn="", desc="test pad",
         pins={"1": "USB_DN"}, sch=(66.04, 177.8, 0)),
    dict(ref="TP8", lib="Connector:TestPoint", value="USB_D+", fp=TP, mpn="", desc="test pad",
         pins={"1": "USB_DP"}, sch=(78.74, 177.8, 0)),
    dict(ref="TP9", lib="Connector:TestPoint", value="VBAT", fp=TP, mpn="", desc="test pad", pins={"1": VBAT},
         sch=(40.64, 203.2, 0)),
    dict(ref="TP10", lib="Connector:TestPoint", value="VBAT_SENSE", fp=TP, mpn="", desc="test pad",
         pins={"1": "VBAT_SENSE"}, sch=(320.04, 231.14, 0)),
]

# Power flags (ERC: these nets are driven by passive parts only): (net, x, y)
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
